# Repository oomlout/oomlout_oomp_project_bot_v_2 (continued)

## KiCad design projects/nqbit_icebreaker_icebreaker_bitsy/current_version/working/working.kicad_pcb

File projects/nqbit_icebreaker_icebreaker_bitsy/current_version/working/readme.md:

# icebreaker
 
## summary 
* id: nqbit_icebreaker_icebreaker_bitsy
* user: nqbit
* name: icebreaker
* board: icebreaker_bitsy
* repo: https://github.com/nqbit/icebreaker
* src_file_repo_kicad_pcb: hardware/bitsy-v0.3a/icebreaker-bitsy.kicad_pcb
* src_file_repo_kicad_pcb_link: https://github.com/nqbit/icebreaker/tree/master/hardware/bitsy-v0.3a/icebreaker-bitsy.kicad_pcb

* src_file_repo_sch: hardware/bitsy-v0.3a/icebreaker-bitsy.sch
* src_file_repo_sch_link: https://github.com/nqbit/icebreaker/tree/master/hardware/bitsy-v0.3a/icebreaker-bitsy.sch
* full details link: https://github.com/oomlout/oomlout_oomp_project_bot_v_2/tree/main/projects/nqbit_icebreaker_icebreaker_bitsy/current_version/working

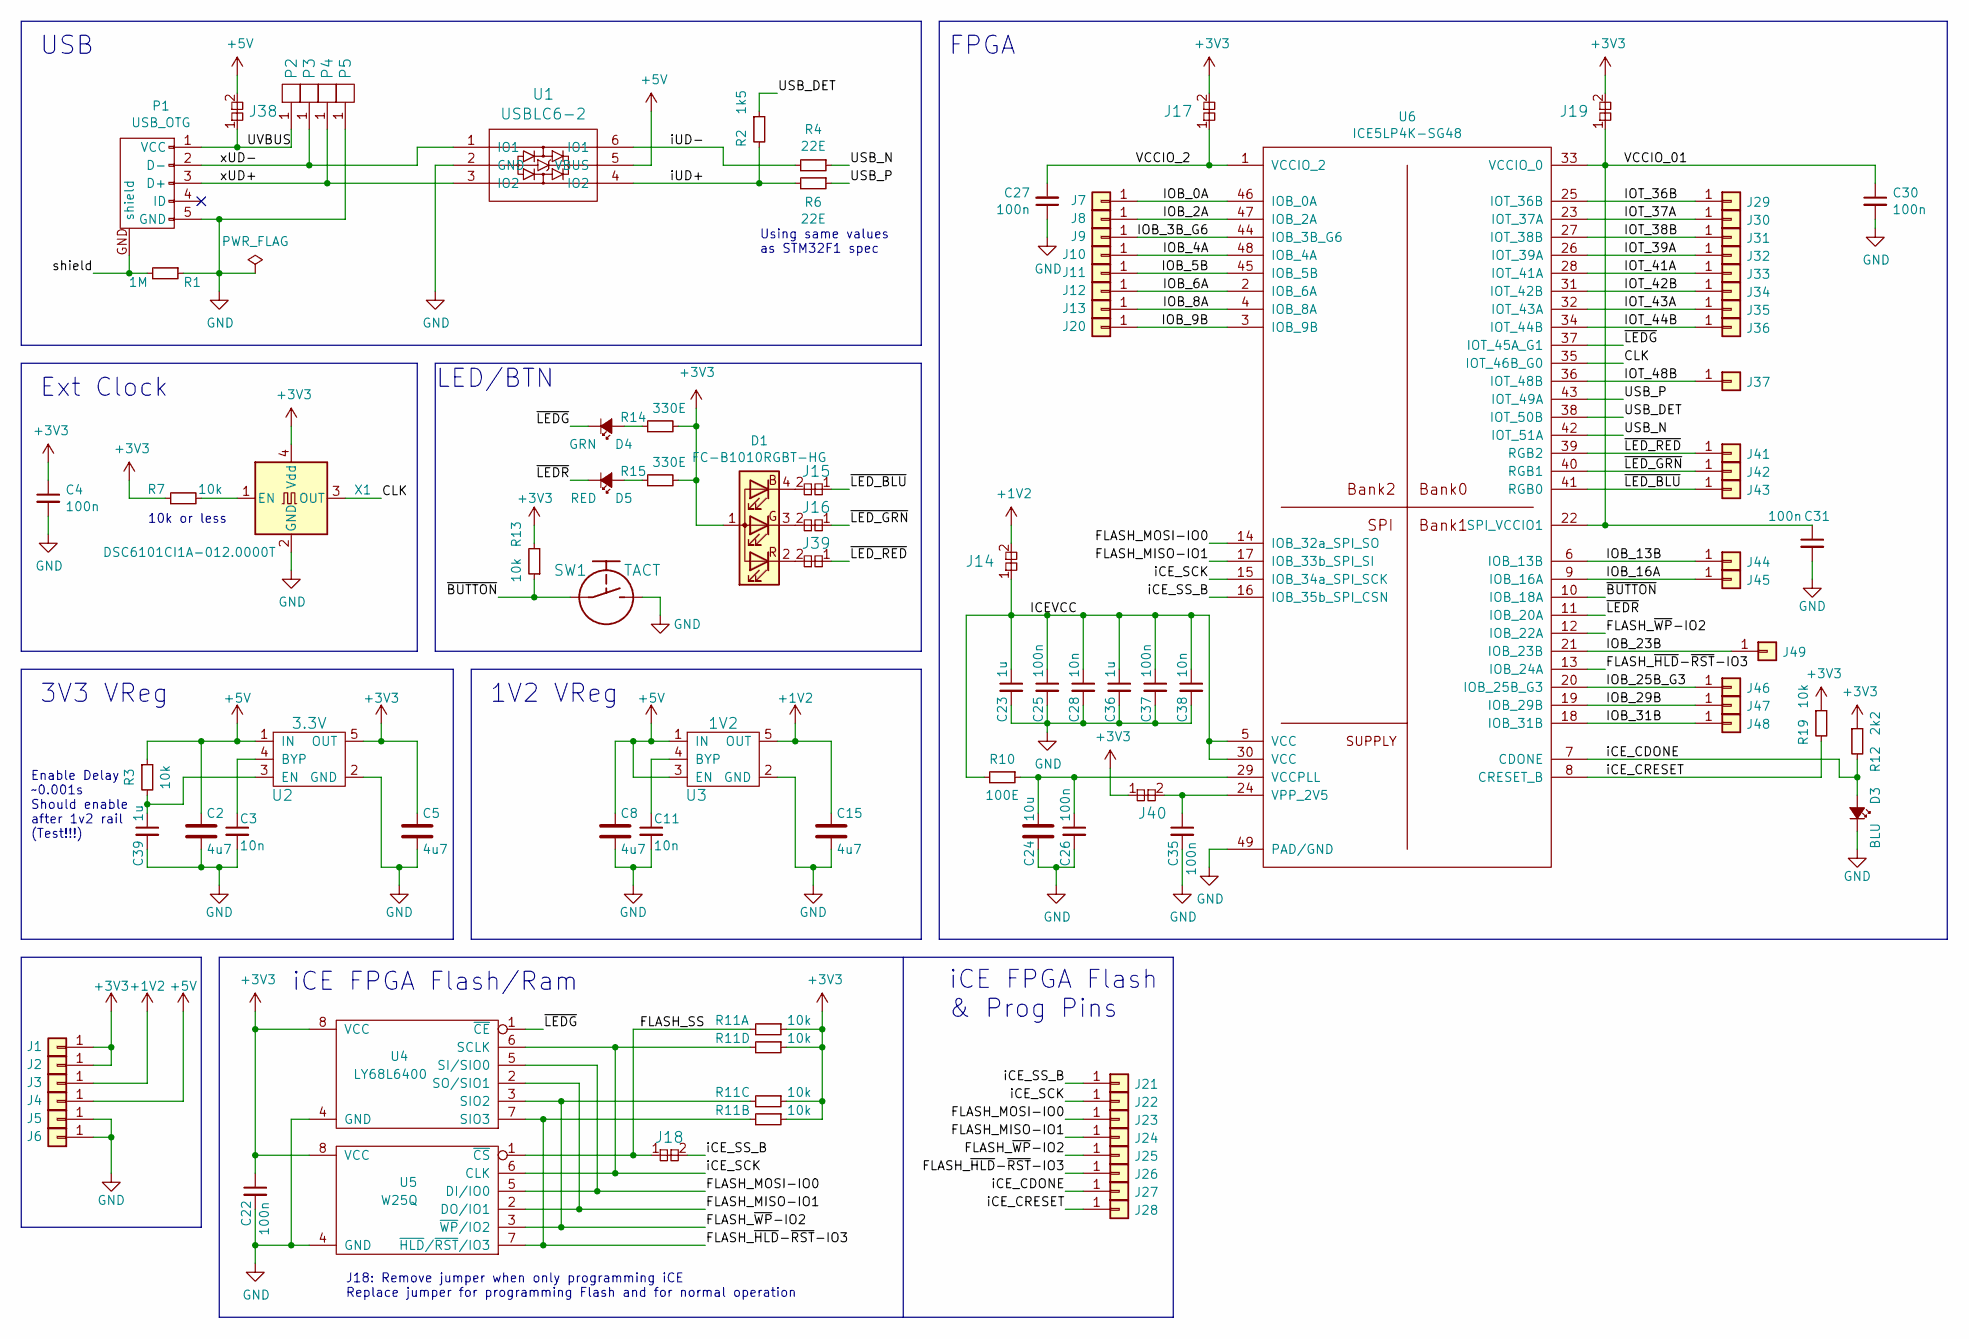
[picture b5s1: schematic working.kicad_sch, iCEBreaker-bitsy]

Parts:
C2, C5, C8, C15: 4u7; C_0603
C3, C11, C28, C38: 10n; C_0402
C4, C22, C25, C26, C27, C30, C31, C35, C37: 100n; C_0402
C23, C36, C39: 1u; C_0402
C24: 10u; C_0603
D1: FC-B1010RGBT-HG; LED_TRI_1010
D3: BLU; D_0603
D4: GRN; D_0603
D5: RED; D_0603
J1, J2, J3, J4, J5, J6, J7, J8, J9, J10, J11, J12, J13, J20, J21, J22, J23, J24, J25, J26, J27, J28, J29, J30, J31, J32, J33, J34, J35, J36, J37, J41, J42, J43, J44, J45, J46, J47, J48, J49: Conn_01x01; Pin_Header_Straight_Round_1x01
J14, J15, J16, J17, J19, J38, J39: Jumper; J_NC_0603_30
J18, J40: Jumper; J_NC_0402_15
P1: USB_OTG; Connector_USB_Micro_B_SMD
P2, P3, P4, P5: UP; PAD_SMD_1x2.65
R1: 1M; R_0402
R2: 1k5; R_0402
R3, R7, R13, R19: 10k; R_0402
R4, R6: 22E; R_0402
R10: 100E; R_0402
R11: 10k; R_Array_Convex_4x0402
R12: 2k2; R_0402
R14, R15: 330E; R_0402
SW1: TACT; SW_SPST_3x4x2.5
U1: USBLC6-2; SOT-666
U2: 3.3V; SOT-23-5
U3: 1V2; SOT-23-5
U4: LY68L6400; SOIC-8_3.9x4.9mm_P1.27mm
U5: W25Q; SOIC-8_5.3x5.3mm_Pitch1.27mm
U6: ICE5LP4K-SG48; QFN-48-1EP_7x7mm_Pitch0.5mm
X1: DSC6101CI1A-012.0000T; Oscillator_SMD_SCTF_S2DXX-4Pin_2.5x2.0mm

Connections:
+1V2: C15.1, J3.1, J14.2, U3.5 (OUT)
+3V3: C4.1, C5.1, C22.1, D1.1 (A), J1.1, J2.1, J17.2, J19.2, J40.1, R7.1, R11.1, R11.3, R11.5, R11.7, R12.1, R13.2, R14.2, R15.2, R19.1, U2.5 (OUT), U4.8 (VCC), U5.8 (VCC), X1.4 (Vdd)
+5V: C2.1, C8.1, J4.1, J38.2, R3.1, U1.5 (VBUS), U2.1 (IN), U3.1 (IN), U3.3 (EN)
/CLK: U6.35 (IOT_46B_G0), X1.3 (OUT)
/FLASH_MISO-IO1: J24.1, U4.2 (SO/SIO1), U5.2 (DO/IO1), U6.17 (IOB_33b_SPI_SI)
/FLASH_MOSI-IO0: J23.1, U4.5 (SI/SIO0), U5.5 (DI/IO0), U6.14 (IOB_32a_SPI_SO)
/FLASH_SS: J18.1, R11.2, U5.1 (~CS)
/FLASH_~HLD-~RST-IO3: J26.1, R11.4, U4.7 (SIO3), U5.7 (~HLD/~RST/IO3), U6.13 (IOB_24A)
/FLASH_~WP-IO2: J25.1, R11.6, U4.3 (SIO2), U5.3 (~WP/IO2), U6.12 (IOB_22A)
/ICEVCC: C23.1, C25.1, C28.1, C36.1, C37.1, C38.1, J14.1, R10.2, U6.5 (VCC), U6.30 (VCC)
/IOB_0A: J7.1, U6.46 (IOB_0A)
/IOB_2A: J8.1, U6.47 (IOB_2A)
/IOB_3B_G6: J9.1, U6.44 (IOB_3B_G6)
/IOB_4A: J10.1, U6.48 (IOB_4A)
/IOB_5B: J11.1, U6.45 (IOB_5B)
/IOB_6A: J12.1, U6.2 (IOB_6A)
/IOB_8A: J13.1, U6.4 (IOB_8A)
/IOB_9B: J20.1, U6.3 (IOB_9B)
/IOB_13B: J44.1, U6.6 (IOB_13B)
/IOB_16A: J45.1, U6.9 (IOB_16A)
/IOB_23B: J49.1, U6.21 (IOB_23B)
/IOB_25B_G3: J46.1, U6.20 (IOB_25B_G3)
/IOB_29B: J47.1, U6.19 (IOB_29B)
/IOB_31B: J48.1, U6.18 (IOB_31B)
/IOT_36B: J29.1, U6.25 (IOT_36B)
/IOT_37A: J30.1, U6.23 (IOT_37A)
/IOT_38B: J31.1, U6.27 (IOT_38B)
/IOT_39A: J32.1, U6.26 (IOT_39A)
/IOT_41A: J33.1, U6.28 (IOT_41A)
/IOT_42B: J34.1, U6.31 (IOT_42B)
/IOT_43A: J35.1, U6.32 (IOT_43A)
/IOT_44B: J36.1, U6.34 (IOT_44B)
/IOT_48B: J37.1, U6.36 (IOT_48B)
/USB_DET: R2.1, U6.38 (IOT_50B)
/USB_N: R4.1, U6.42 (IOT_51A)
/USB_P: R6.1, U6.43 (IOT_49A)
/UVBUS: J38.1, P1.1 (VCC), P2.1
/VCCIO_01: C30.1, C31.1, J19.1, U6.22 (SPI_VCCIO1), U6.33 (VCCIO_0)
/VCCIO_2: C27.2, J17.1, U6.1 (VCCIO_2)
/iCE_CDONE: D3.A, J27.1, R12.2, U6.7 (CDONE)
/iCE_CRESET: J28.1, R19.2, U6.8 (CRESET_B)
/iCE_SCK: J22.1, R11.8, U4.6 (SCLK), U5.6 (CLK), U6.15 (IOB_34a_SPI_SCK)
/iCE_SS_B: J18.2, J21.1, U6.16 (IOB_35b_SPI_CSN)
/iUD+: R2.2, R6.2, U1.4 (IO2)
/iUD-: R4.2, U1.6 (IO1)
/shield: P1.GND (shield), R1.2
/xUD+: P1.3 (D+), P4.1, U1.3 (IO2)
/xUD-: P1.2 (D-), P3.1, U1.1 (IO1)
/~BUTTON: R13.1, SW1.1, U6.10 (IOB_18A)
/~LEDG: D4.C, U4.1 (~CE), U6.37 (IOT_45A_G1)
/~LEDR: D5.C, U6.11 (IOB_20A)
/~LED_BLU: J15.1, J43.1, U6.41 (RGB0)
/~LED_GRN: J16.1, J42.1, U6.40 (RGB1)
/~LED_RED: J39.1, J41.1, U6.39 (RGB2)
GND: C2.2, C3.2, C4.2, C5.2, C8.2, C11.2, C15.2, C22.2, C23.2, C24.2, C25.2, C26.2, C27.1, C28.2, C30.2, C31.2, C35.2, C36.2, C37.2, C38.2, C39.2, D3.C, J5.1, J6.1, P1.5 (GND), P5.1, R1.1, SW1.2, U1.2 (GND), U2.2 (GND), U3.2 (GND), U4.4 (GND), U5.4 (GND), U6.49 (PAD/GND), X1.2 (GND)
unnamed: C3.1, U2.4 (BYP)
unnamed: C11.1, U3.4 (BYP)
unnamed: C24.1, C26.1, R10.1, U6.29 (VCCPLL)
unnamed: C35.1, J40.2, U6.24 (VPP_2V5)
unnamed: C39.1, R3.2, U2.3 (EN)
unnamed: D1.2 (RK), J39.2
unnamed: D1.3 (GK), J16.2
unnamed: D1.4 (BK), J15.2
unnamed: D4.A, R14.1
unnamed: D5.A, R15.1
unnamed: R7.2, X1.1 (EN)

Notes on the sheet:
Ext Clock
USB
J18: Remove jumper when only programming iCE Replace jumper for programming Flash and for normal operation
1V2 VReg
3V3 VReg
FPGA
Using same values as STM32F1 spec
LED/BTN
10k or less
iCE FPGA Flash/Ram
iCE FPGA Flash & Prog Pins
Enable Delay ~0.001s Should enable after 1v2 rail (Test!!!)

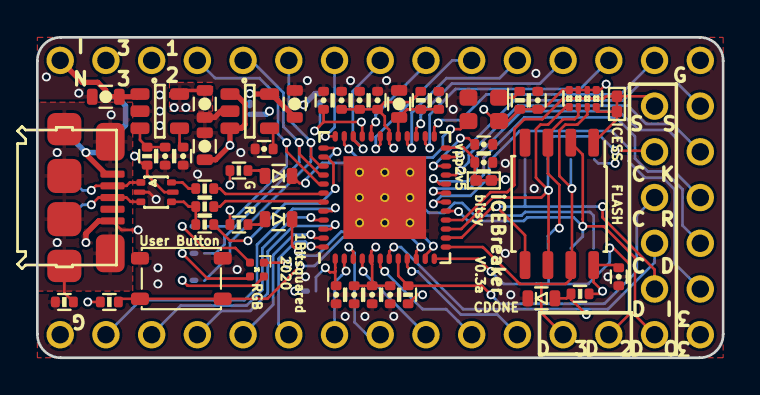
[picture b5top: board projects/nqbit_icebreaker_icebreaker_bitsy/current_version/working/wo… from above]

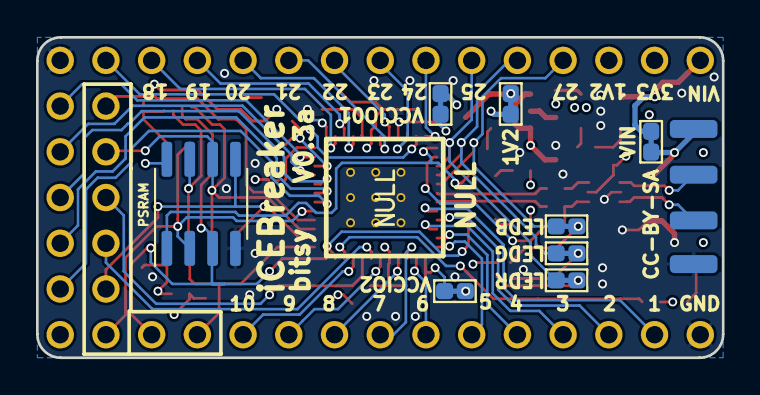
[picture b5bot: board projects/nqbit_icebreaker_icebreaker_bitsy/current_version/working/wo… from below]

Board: 4 copper layers, 38.1 x 17.8 mm, 100 parts (12 on the bottom side), 66 nets.

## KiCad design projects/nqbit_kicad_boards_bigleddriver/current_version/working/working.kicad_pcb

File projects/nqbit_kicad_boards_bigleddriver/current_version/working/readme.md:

# kicad_boards
 
## summary 
* id: nqbit_kicad_boards_bigleddriver
* user: nqbit
* name: kicad_boards
* board: bigleddriver
* repo: https://github.com/nqbit/kicad-boards
* src_file_repo_kicad_pcb: bigleddriver/bigleddriver.kicad_pcb
* src_file_repo_kicad_pcb_link: https://github.com/nqbit/kicad-boards/tree/master/bigleddriver/bigleddriver.kicad_pcb

* src_file_repo_sch: bigleddriver/bigleddriver.sch
* src_file_repo_sch_link: https://github.com/nqbit/kicad-boards/tree/master/bigleddriver/bigleddriver.sch
* full details link: https://github.com/oomlout/oomlout_oomp_project_bot_v_2/tree/main/projects/nqbit_kicad_boards_bigleddriver/current_version/working

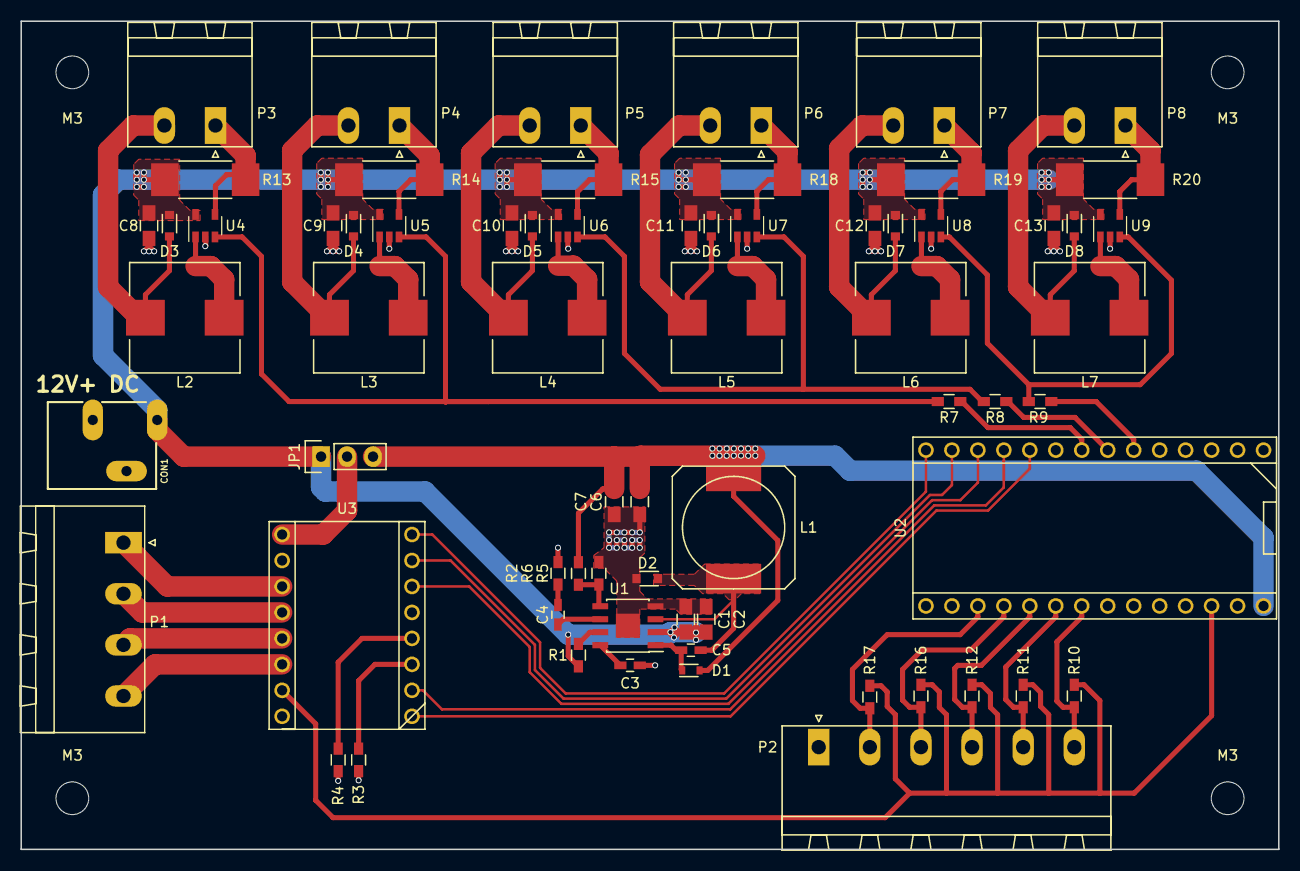
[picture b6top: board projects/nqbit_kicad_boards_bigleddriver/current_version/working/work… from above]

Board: 2 copper layers, 123.0 x 81.0 mm, 71 parts (0 on the bottom side), 52 nets.

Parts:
C1, C2, C8, C9, C10, C11, C12, C13: 10uF; C_0805_HandSoldering
C3: 0.1uF; C_0603_HandSoldering
C4: 3.9nF; C_0603_HandSoldering
C5: 10nF; C_0603_HandSoldering
C6, C7: 22uF; C_0805_HandSoldering
CON1: DC_BARREL_JACK; POWER_JACK_SLOT
D1: IN4148; D_0603
D2: MBRS130; D_0805
D3, D4, D5, D6, D7, D8: 1N5819; D_0805
JP1: Jumper_NC_Dual; Pin_Header_Straight_1x03
L1: 10uH; SELF-WE-PD-XXL
L2, L3, L4, L5, L6, L7: 100uH; Inductor_Wurth_HCI-1030
M3, M3#2, M3#3, M3#4: MountingHole_3.2mm_M3
P1: CONN_01X04; PhoenixContact_MSTBA-G_04x5.00mm_Angled
P2: CONN_01X06; PhoenixContact_MSTBA-G_06x5.00mm_Angled
P3, P4, P5, P6, P7, P8: CONN_01X02; PhoenixContact_MSTBA-G_02x5.00mm_Angled
R1: 100k; R_0603_HandSoldering
R2: 6.8k; R_0603_HandSoldering
R3, R4: 0; R_0603_HandSoldering
R5, R10, R11, R12, R16, R17: 10k; R_0603_HandSoldering
R6: 44.2k; R_0603_HandSoldering
R7, R8, R9: 22; R_0603_HandSoldering
R13, R14, R15, R18, R19, R20: 0.3; R_2512_HandSoldering
U1: MP2307; SOIC-8-1EP_3.9x4.9mm_Pitch1.27mm
U2: TEENSY_3.2
U3: STEP_STICK_TMC2208; TMC2208_SILENTSTEPSTICK
U4, U5, U6, U7, U8, U9: AL8861; SOT-23-5

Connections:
+5V: C6.1, C7.1, D1.2, JP1.3, L1.2, R6.2, U2.28
+12V: C1.1, C2.1, C8.1, C9.1, C10.1, C11.1, C12.1, C13.1, CON1.PWR, D3.1, D4.1, D5.1, D6.1, D7.1, D8.1, JP1.1, R1.2, R13.2, R14.2, R15.2, R18.2, R19.2, R20.2, U1.2, U4.5, U5.5, U6.5, U7.5, U8.5, U9.5
/BTN0: P2.6, R10.2, U2.21
/BTN1: P2.5, R11.2, U2.20
/BTN2: P2.4, R12.2, U2.19
/BTN3: P2.3, R16.2, U2.18
/BTN4: P2.2, R17.2, U2.17
/M1-A: P1.3, U3.13
/M1-B: P1.4, U3.14
/M2-A: P1.2, U3.12
/M2-B: P1.1, U3.11
/MOTOR_DIR: U2.10, U3.1
/MOTOR_EN: U2.14, U3.8
/MOTOR_MS1: U2.13, U3.7
/MOTOR_MS2: U2.12, U3.6
/MOTOR_STEP: U2.11, U3.2
/PWM_B: R9.1, U8.3, U9.3
/PWM_G: R8.1, U6.3, U7.3
/PWM_R: R7.1, U4.3, U5.3
/SW: C5.2, D2.1, L1.1, U1.3
/VIO: R10.1, R11.1, R12.1, R16.1, R17.1, U2.26, U3.15
GND: C1.2, C2.2, C3.2, C6.2, C7.2, C8.2, C9.2, C10.2, C11.2, C12.2, C13.2, CON1.GND@, D2.2, P2.1, R2.1, R3.2, R4.2, R5.2, U1.4, U1.9, U2.1, U2.27, U3.10, U3.16, U4.2, U5.2, U6.2, U7.2, U8.2, U9.2
unnamed: C3.1, U1.8
unnamed: C4.1, U1.6
unnamed: C4.2, R2.2
unnamed: C5.1, D1.1, U1.1
unnamed: D3.2, L2.2, P3.2
unnamed: D4.2, L3.2, P4.2
unnamed: D5.2, L4.2, P5.2
unnamed: D6.2, L5.2, P6.2
unnamed: D7.2, L6.2, P7.2
unnamed: D8.2, L7.2, P8.2
unnamed: L2.1, U4.1
unnamed: L3.1, U5.1
unnamed: L4.1, U6.1
unnamed: L5.1, U7.1
unnamed: L6.1, U8.1
unnamed: L7.1, U9.1
unnamed: P3.1, R13.1, U4.4
unnamed: P4.1, R14.1, U5.4
unnamed: P5.1, R15.1, U6.4
unnamed: P6.1, R18.1, U7.4
unnamed: P7.1, R19.1, U8.4
unnamed: P8.1, R20.1, U9.4
unnamed: R1.1, U1.7
unnamed: R3.1, U3.3
unnamed: R4.1, U3.4
unnamed: R5.1, R6.1, U1.5
unnamed: R7.2, U2.8
unnamed: R8.2, U2.7
unnamed: R9.2, U2.6
VMOTOR: JP1.2, U3.9

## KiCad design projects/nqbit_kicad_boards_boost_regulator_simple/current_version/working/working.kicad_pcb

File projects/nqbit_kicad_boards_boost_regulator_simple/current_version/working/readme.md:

# kicad_boards
 
## summary 
* id: nqbit_kicad_boards_boost_regulator_simple
* user: nqbit
* name: kicad_boards
* board: boost_regulator_simple
* repo: https://github.com/nqbit/kicad-boards
* src_file_repo_kicad_pcb: boost_regulator_simple/boost_regulator_simple.kicad_pcb
* src_file_repo_kicad_pcb_link: https://github.com/nqbit/kicad-boards/tree/master/boost_regulator_simple/boost_regulator_simple.kicad_pcb

* src_file_repo_sch: boost_regulator_simple/boost_regulator_simple.sch
* src_file_repo_sch_link: https://github.com/nqbit/kicad-boards/tree/master/boost_regulator_simple/boost_regulator_simple.sch
* full details link: https://github.com/oomlout/oomlout_oomp_project_bot_v_2/tree/main/projects/nqbit_kicad_boards_boost_regulator_simple/current_version/working

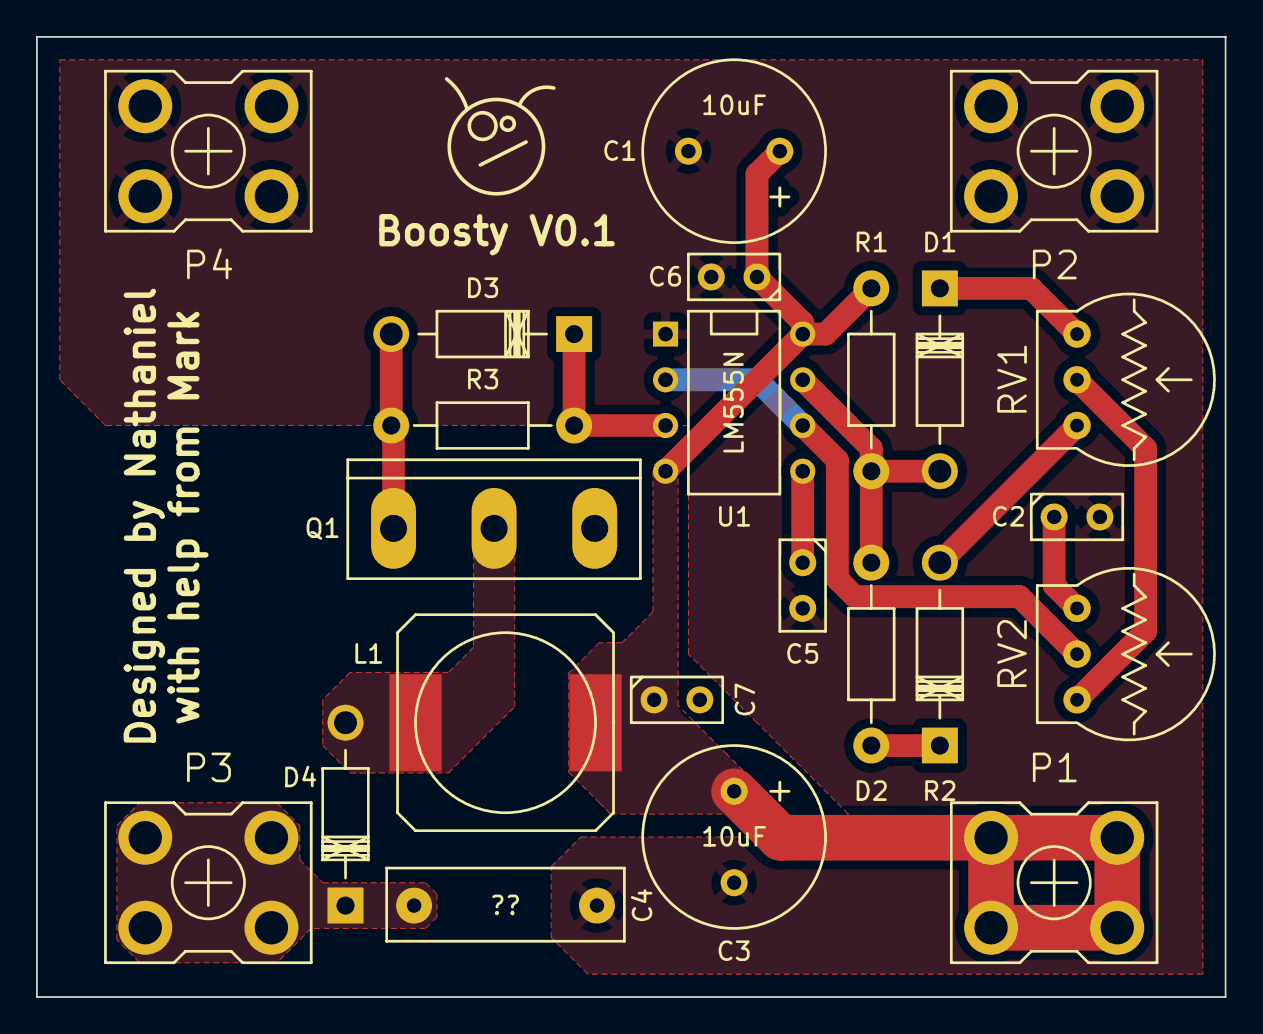
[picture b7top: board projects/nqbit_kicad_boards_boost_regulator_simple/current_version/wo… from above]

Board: 2 copper layers, 66.0 x 53.3 mm, 23 parts (0 on the bottom side), 14 nets.

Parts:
C1, C3: 10uF; Elko_vert_20x10mm_RM5
C2: 1uF; Capacitor3MMDiscRM2.5
C4: ??; Capacitor13x4RM10
C5, C6, C7: 0.01uF; Capacitor3MMDiscRM2.5
D1, D2, D3, D4: DIODE; Diode_DO-41_SOD81_Horizontal_RM10
L1: INDUCTOR; SELF-WE-PD-XXL
P1, P2, P3, P4: CONN_01X01; Screw_Terminal_x1
Q1: MOSFET-N; TO-247_Vertical_Neutral123
R1, R2, R3: 1k; Resistor_Horizontal_RM10mm
RV1, RV2: 1k; Potentiometer_Thumbwheel
U1: LM555N; DIP-8__300

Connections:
/BOOST_OUT: C4.1, D4.2, P3.1
GND: C1.2, C2.2, C3.2, C4.2, C5.2, C6.2, C7.2, P2.1, P4.1, Q1.3, U1.1
unnamed: C2.1, RV2.3
unnamed: C5.1, U1.5
unnamed: D1.1, R1.2, R2.1, U1.7
unnamed: D1.2, RV1.3
unnamed: D2.1, RV1.1
unnamed: D2.2, R2.2
unnamed: D3.1, Q1.1, R3.1
unnamed: D3.2, R3.2, U1.3
unnamed: D4.1, L1.2, Q1.2
unnamed: RV1.2, RV2.1
unnamed: RV2.2, U1.2, U1.6
VCC: C1.1, C3.1, C6.1, C7.1, L1.1, P1.1, R1.1, U1.4, U1.8
